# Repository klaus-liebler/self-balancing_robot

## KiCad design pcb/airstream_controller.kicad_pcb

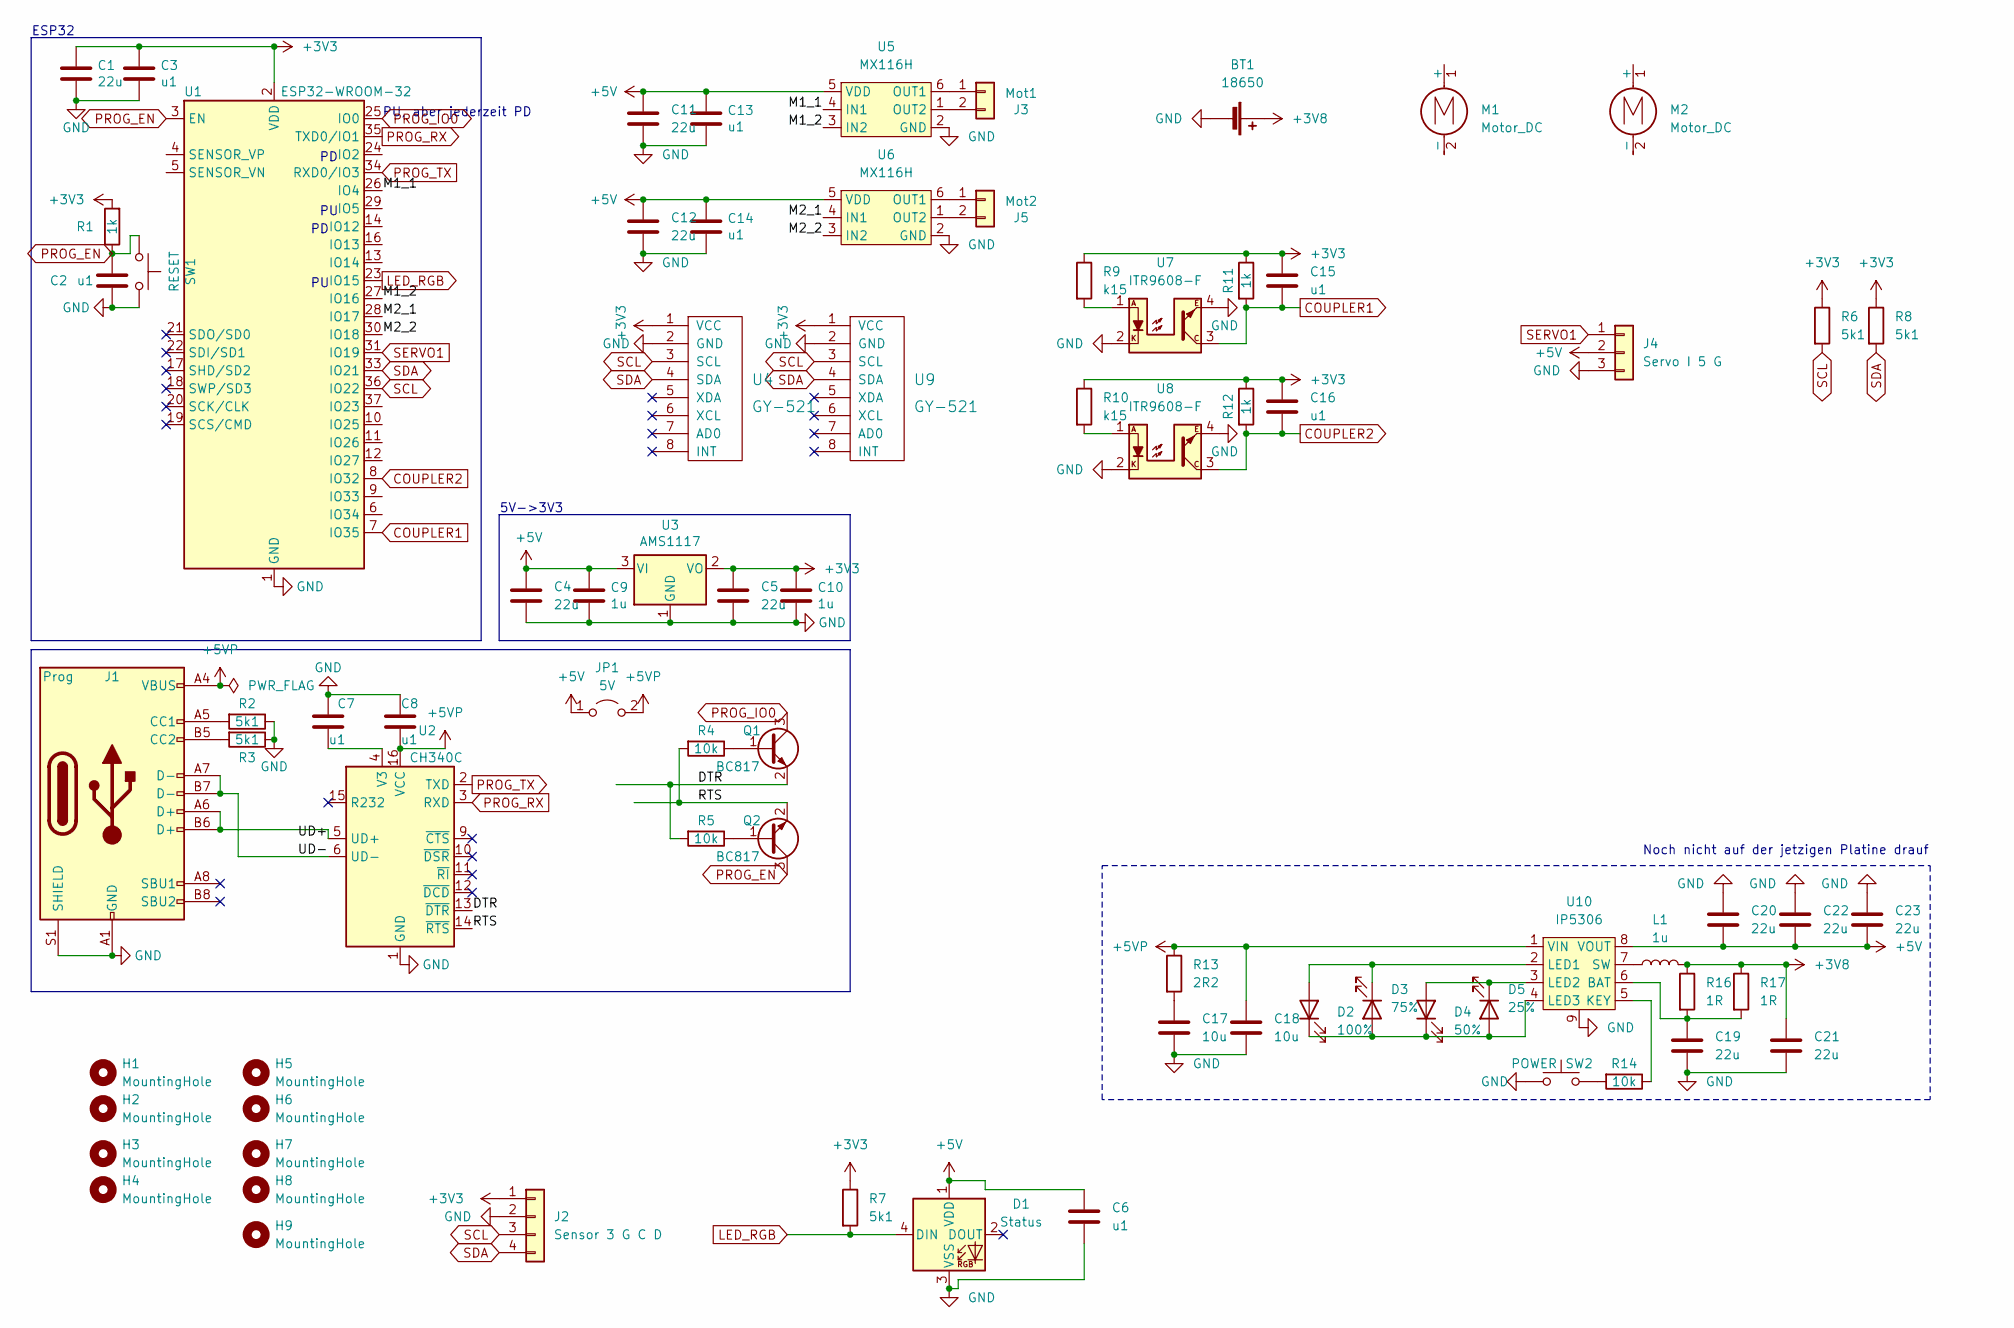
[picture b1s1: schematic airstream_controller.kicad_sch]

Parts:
BT1: 18650; BatteryHolder_MPD_BH-18650-PC2
C1, C4, C5, C11, C12, C19, C20, C21, C22, C23: 22u; C_0603_1608Metric
C2, C3, C6, C7, C8, C13, C14, C15, C16: u1; C_0603_1608Metric
C9, C10: 1u; C_0603_1608Metric
C17, C18: 10u; C_0603_1608Metric
D1: Status; LED_WS2812B_PLCC4_5.0x5.0mm_P3.2mm
D2: 100%; LED_0603_1608Metric
D3: 75%; LED_0603_1608Metric
D4: 50%; LED_0603_1608Metric
D5: 25%; LED_0603_1608Metric
H1, H2, H3, H4, H5, H6, H7, H8, H9: MountingHole; MountingHole_3.2mm_M3
J1: Prog; USB_C_Receptacle_HRO_TYPE-C-31-M-12
J2: Sensor 3 G C D; JST_XH_B4B-XH-A_1x04_P2.50mm_Vertical
J3: Mot1; JST_XH_B2B-XH-A_1x02_P2.50mm_Vertical
J4: Servo I 5 G; PinHeader_1x03_P2.54mm_Vertical
J5: Mot2; JST_XH_B2B-XH-A_1x02_P2.50mm_Vertical
JP1: 5V; SolderJumper-2_P1.3mm_Open_RoundedPad1.0x1.5mm
L1: 1u; L_Abracon_ASPI-0630LR
M1, M2: Motor_DC; TT-Motor
Q1, Q2: BC817; SOT-23
R1, R11, R12: 1k; R_0603_1608Metric
R2, R3, R6, R7, R8: 5k1; R_0603_1608Metric
R4, R5, R14: 10k; R_0603_1608Metric
R9, R10: k15; R_0603_1608Metric
R13: 2R2; R_0603_1608Metric
R16, R17: 1R; R_0603_1608Metric
SW1: RESET; SW_SPST_TL3342
SW2: POWER; SW_SPST_TL3342
U1: ESP32-WROOM-32
U2: CH340C; SOIC-16_3.9x9.9mm_P1.27mm
U3: AMS1117; SOT-223-3_TabPin2
U4, U9: GY-521
U5, U6: MX116H; SOT-23-6
U7, U8: ITR9608-F; ITR9608_recessed
U10: IP5306; HSOP-8-1EP_3.9x4.9mm_P1.27mm_EP2.3x2.3mm_ThermalVias

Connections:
+3V3: C1.1, C3.2, C5.1, C10.1, C15.1, C16.1, J2.1, R1.2, R6.1, R7.1, R8.1, R9.1, R10.1, R11.1, R12.1, U1.2 (VDD), U3.2 (VO), U4.1 (VCC), U9.1 (VCC)
+3V8: BT1.1 (+), C21.1, L1.2, R16.1, R17.1
+5V: C4.1, C6.1, C9.1, C11.1, C12.1, C13.1, C14.1, C20.2, C22.2, C23.2, D1.1 (VDD), J4.2, JP1.1 (A), U3.3 (VI), U5.5 (VDD), U6.5 (VDD), U10.8 (VOUT)
+5VP: C8.1, C18.1, J1.A4 (VBUS), J1.A9 (VBUS), J1.B4 (VBUS), J1.B9 (VBUS), JP1.2 (B), R13.1, U2.16 (VCC), U10.1 (VIN)
/DTR: Q1.2 (E), R5.2, U2.13 (~DTR)
/M1_1: U1.26 (IO4), U5.4 (IN1)
/M1_2: U1.27 (IO16), U5.3 (IN2)
/M2_1: U1.28 (IO17), U6.4 (IN1)
/M2_2: U1.30 (IO18), U6.3 (IN2)
/RTS: Q2.2 (E), R4.2, U2.14 (~RTS)
/UD+: J1.A6 (D+), J1.B6 (D+), U2.5 (UD+)
/UD-: J1.A7 (D-), J1.B7 (D-), U2.6 (UD-)
COUPLER1: C15.2, R11.2, U1.7 (IO35), U7.3
COUPLER2: C16.2, R12.2, U1.8 (IO32), U8.3
GND: BT1.2 (-), C1.2, C2.1, C3.1, C4.2, C5.2, C6.2, C7.2, C8.2, C9.2, C10.2, C11.2, C12.2, C13.2, C14.2, C17.2, C18.2, C19.2, C20.1, C21.2, C22.1, C23.1, D1.3 (VSS), J1.A1 (GND), J1.A12 (GND), J1.B1 (GND), J1.B12 (GND), J1.S1 (SHIELD), J2.2, J4.3, R2.1, R3.1, SW1.2, SW2.1, U1.1 (GND), U1.15 (GND), U1.38 (GND), U1.39 (GND), U2.1 (GND), U3.1 (GND), U4.2 (GND), U5.2 (GND), U6.2 (GND), U7.2, U7.4, U8.2, U8.4, U9.2 (GND), U10.9
LED_RGB: D1.4 (DIN), R7.2, U1.23 (IO15)
unnamed: C7.1, U2.4 (V3)
unnamed: C17.1, R13.2
unnamed: C19.1, R16.2, R17.2, U10.6 (BAT)
unnamed: D2.1 (K), D3.2 (A), D4.1 (K), D5.2 (A), U10.4 (LED3)
unnamed: D2.2 (A), D3.1 (K), U10.2 (LED1)
unnamed: D4.2 (A), D5.1 (K), U10.3 (LED2)
unnamed: J1.A5 (CC1), R2.2
unnamed: J1.B5 (CC2), R3.2
unnamed: J3.1, U5.6 (OUT1)
unnamed: J3.2, U5.1 (OUT2)
unnamed: J5.1, U6.6 (OUT1)
unnamed: J5.2, U6.1 (OUT2)
unnamed: L1.1, U10.7 (SW)
unnamed: Q1.1 (B), R4.1
unnamed: Q2.1 (B), R5.1
unnamed: R9.2, U7.1
unnamed: R10.2, U8.1
unnamed: R14.1, U10.5 (KEY)
unnamed: R14.2, SW2.2
PROG_EN: C2.2, Q2.3 (C), R1.1, SW1.1, U1.3 (EN)
PROG_IO0: Q1.3 (C), U1.25 (IO0)
PROG_RX: U1.35 (TXD0/IO1), U2.3 (RXD)
PROG_TX: U1.34 (RXD0/IO3), U2.2 (TXD)
SCL: J2.3, R6.2, U1.36 (IO22), U4.3 (SCL), U9.3 (SCL)
SDA: J2.4, R8.2, U1.33 (IO21), U4.4 (SDA), U9.4 (SDA)
SERVO1: J4.1, U1.31 (IO19)

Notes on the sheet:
PU, aber jederzeit PD
ESP32
5V->3V3
Noch nicht auf der jetzigen Platine drauf

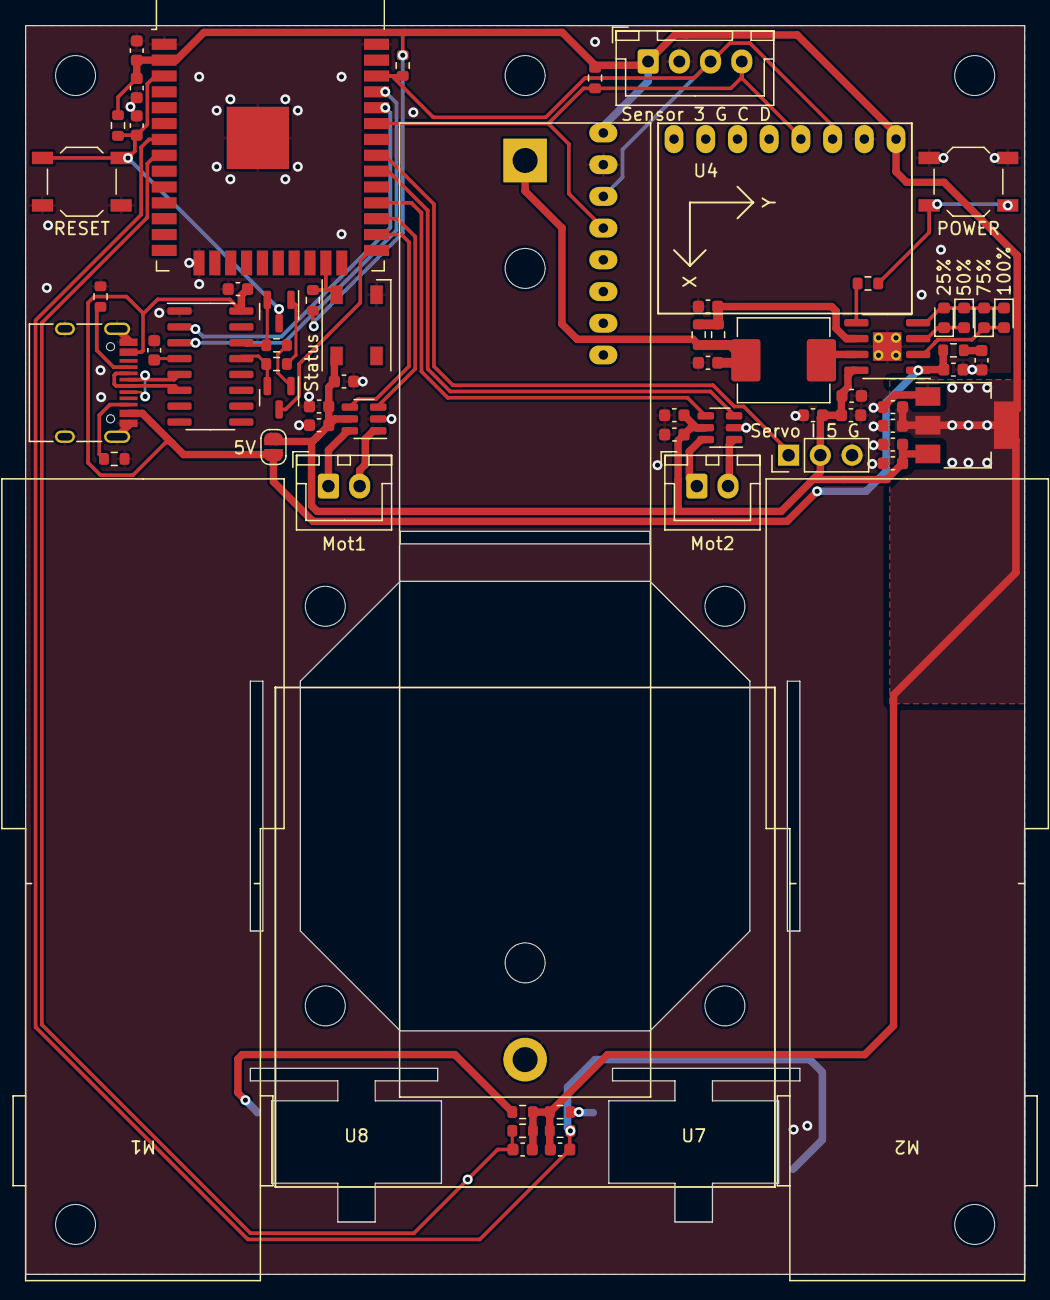
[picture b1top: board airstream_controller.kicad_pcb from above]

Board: 2 copper layers, 80.0 x 100.0 mm, 77 parts (1 on the bottom side), 42 nets.

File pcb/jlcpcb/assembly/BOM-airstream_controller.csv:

Comment,Designator,Footprint,LCSC
u1,"C13,C14,C2,C3,C6,C7,C8",C_0603_1608Metric,C14663
1u,"C10,C9",C_0603_1608Metric,C15849
Prog,J1,USB_C_Receptacle_HRO_TYPE-C-31-M-12,C167321
1k,R1,R_0603_1608Metric,C21190
k15,"R10,R9",R_0603_1608Metric,C22808
5k1,"R2,R3,R6,R7,R8",R_0603_1608Metric,C23186
10k,"R11,R12,R4,R5",R_0603_1608Metric,C25804
Status,D1,LED_WS2812B_PLCC4_5.0x5.0mm_P3.2mm,C2843785
MX116H,"U5,U6",SOT-23-6,C2845121
RESET,SW1,SW_SPST_TL3342,C318884
22u,"C1,C11,C12,C4,C5",C_0603_1608Metric,C59461
AMS1117,U3,SOT-223-3_TabPin2,C6186
ESP32-WROOM-32,U1,ESP32-WROOM-32,C701342
CH340C,U2,SOIC-16_3.9x9.9mm_P1.27mm,C84681
BC817,"Q1,Q2",SOT-23,C8512
MountingHole,H8,MountingHole_3.2mm_M3,
MountingHole,H7,MountingHole_3.2mm_M3,
MountingHole,H6,MountingHole_3.2mm_M3,
MountingHole,H5,MountingHole_3.2mm_M3,
Mot1,J3,JST_XH_B2B-XH-A_1x02_P2.50mm_Vertical,
MountingHole,H2,MountingHole_3.2mm_M3,
MountingHole,H4,MountingHole_3.2mm_M3,
MountingHole,H3,MountingHole_3.2mm_M3,
Sensor 3 C D G,J2,JST_XH_B4B-XH-A_1x04_P2.50mm_Vertical,
MountingHole,H1,MountingHole_3.2mm_M3,
Servo I 5 G,J4,PinHeader_1x03_P2.54mm_Vertical,
GY-521,U9,GY-521,
Motor_DC,M1,TT-Motor,
Mot2,J5,JST_XH_B2B-XH-A_1x02_P2.50mm_Vertical,
18650,BT1,BatteryHolder_MPD_BH-18650-PC2,
MountingHole,H9,MountingHole_3.2mm_M3,
ITR9608,U7,ITR9608_recessed,
GY-521,U4,GY-521,
Motor_DC,M2,TT-Motor,
ITR9608,U8,ITR9608_recessed,
4V GN GN 5V,J6,PinHeader_1x04_P2.54mm_Vertical,

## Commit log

2024-01-03 New Kicad Version
